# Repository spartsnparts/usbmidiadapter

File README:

To build this firmware, copy the entire directory into the Projects subfolder
in you LUFA build directory. This firmware was written for and built against
version 120730 of the LUFA library.

The USB processing portion of the code should be fairly universal. The portion
of the code responsible for handling serial communication between the adapter
and a controller is specific to the ATMega8/16u2 line of microcontrollers. It
should be fairly easy to adapt for different chips however, simply consult
the datasheet for whatever chip you want to use and substitute the appropriate
registers.

This project, and any code contained within it, is licensed under the MIT
License.

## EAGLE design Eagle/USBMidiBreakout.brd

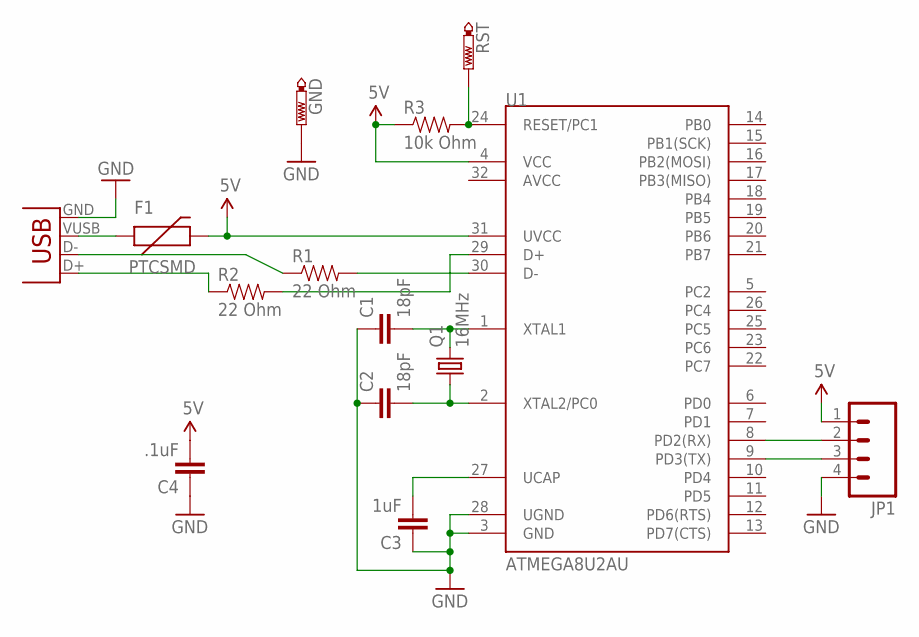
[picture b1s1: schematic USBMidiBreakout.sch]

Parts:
C1, C2: 18pF; 1206
C3: 1uF; 1206
C4: .1uF; 1206
F1: PTCSMD; PTC-1206
GND: PTR1B1,27; B1,27
JP1: M04PTH; 1X04
Q1: 16MHz; HC49UP
R1, R2: 22 Ohm; 1206
R3: 10k Ohm; 1206
RST: PTR1B1,27; B1,27
U1: ATMEGA8U2AU; TQFP32-08
X1: USB-B-S; USB-B-SMT

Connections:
5V: C4.2, F1.2, JP1.1, R3.1, U1.4 (VCC), U1.31 (UVCC)
GND: C1.1, C2.1, C3.1, C4.1, GND.TP, JP1.4, U1.3 (GND), U1.28 (UGND), X1.GND
unnamed: C3.2, U1.27 (UCAP)
unnamed: C1.2, Q1.2, U1.1 (XTAL1)
unnamed: C2.2, Q1.1, U1.2 (XTAL2/PC0)
unnamed: F1.1, X1.VUSB (VBUS)
unnamed: R1.1, X1.D-
unnamed: R2.1, X1.D+
unnamed: JP1.2, U1.8 (PD2(RX))
unnamed: JP1.3, U1.9 (PD3(TX))
unnamed: R2.2, U1.29 (D+)
unnamed: R1.2, U1.30 (D-)
unnamed: R3.2, RST.TP, U1.24 (RESET/PC1)

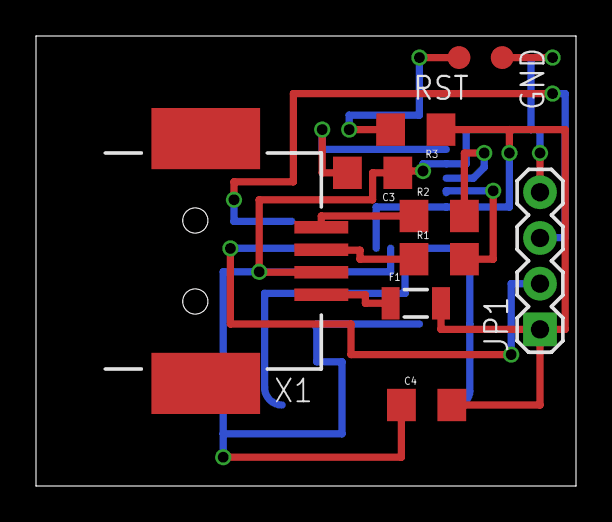
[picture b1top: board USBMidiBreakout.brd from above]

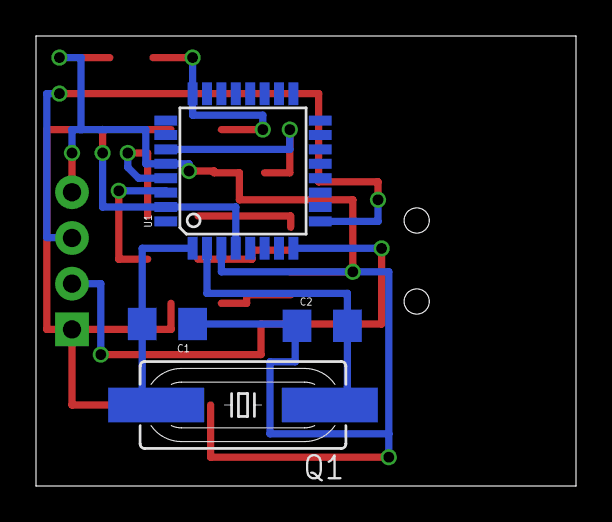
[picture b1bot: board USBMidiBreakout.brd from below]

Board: 2 copper layers, 30.0 x 25.0 mm, 14 parts (4 on the bottom side), 13 nets.

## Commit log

2013-01-23 Initial Project Commit
2013-01-23 Added README
2013-01-23 Added LICENSE file
2013-01-23 Added Eagle board and schematic files for project
2013-01-30 Cleaned up documentation. Added Doxygen configuration file.
2013-01-30 Actual commit of new documentation.

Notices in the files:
parts and their libraries:
SparkFun: Licensing: CC v3.0 Share-Alike You are welcome to use this library for commercial purposes.
